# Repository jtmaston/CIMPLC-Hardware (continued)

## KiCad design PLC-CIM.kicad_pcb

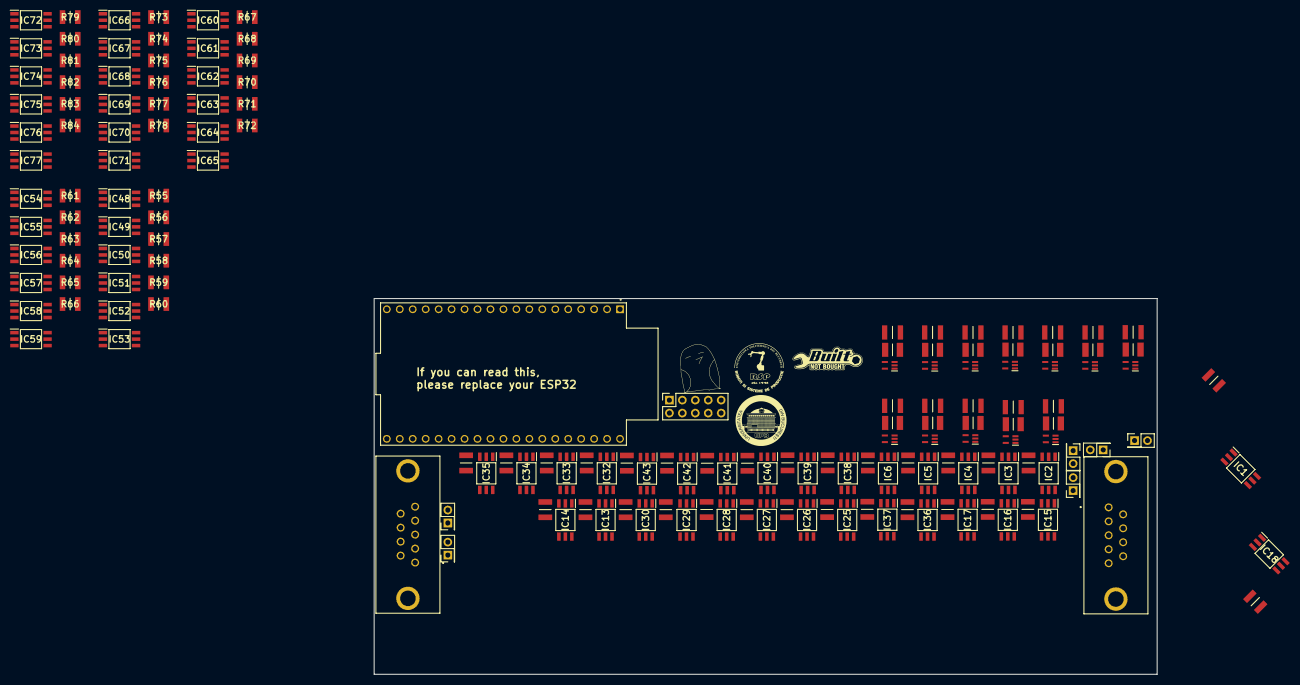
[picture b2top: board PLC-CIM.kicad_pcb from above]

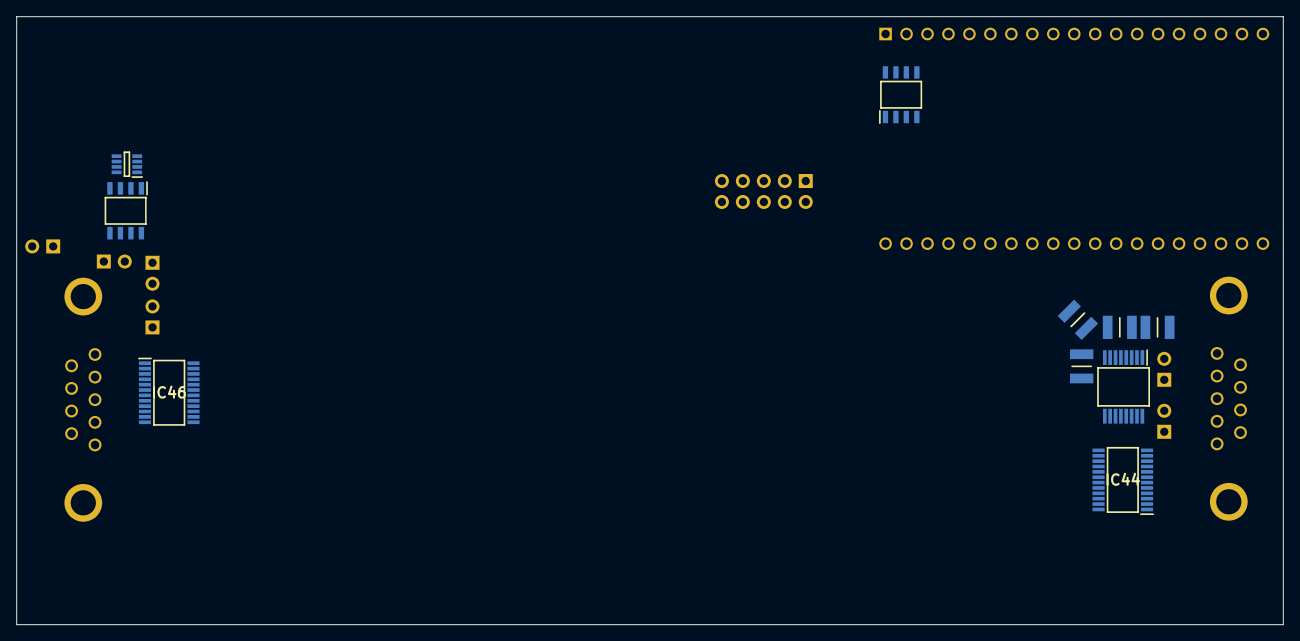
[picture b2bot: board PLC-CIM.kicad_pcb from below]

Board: 4 copper layers, 153.5 x 73.7 mm, 176 parts (10 on the bottom side), 177 nets, no tracks yet.

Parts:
C1, C2, C3, C4: 12103C104KAT2A; CAPC3325X94N
IC1, IC2, IC3, IC4, IC5, IC6, IC13, IC14, IC15, IC16, IC17, IC18, IC25, IC26, IC27, IC28, IC29, IC30, IC32, IC33, IC34, IC35, IC36, IC37, IC38, IC39, IC40, IC41, IC42, IC43, IC48, IC49, IC50, IC51, IC52, IC53, IC54, IC55, IC56, IC57, IC58, IC59, IC60, IC61, IC62, IC63, IC64, IC65, IC66, IC67, IC68, IC69, IC70, IC71, IC72, IC73, IC74, IC75, IC76, IC77: TLP172AM_TPR,E; SOIC127P700X230-6N
IC7, IC8, IC9, IC10, IC11, IC12, IC19, IC20, IC21, IC22, IC23, IC24: TLV9351IDCKR; SOT65P210X110-5N
IC31: MAX3221IDBRE4; SOP65P780X200-16N
IC44, IC46: PCA9555PW,118; SOP65P640X110-24N
IC45: TCAN337DCNR; SOT65P280X145-8N
IC47: SN65HVD75DR; SOIC127P600X175-8N
J8, J13: 750678-1; 7506781
J9, J10, J14, J15, J16, J17: Conn_02x01; PinHeader_2x01_P2.54mm_Vertical
J11: Conn_02x05_Odd_Even; PinSocket_2x05_P2.54mm_Vertical
R1, R2, R3, R4, R5, R6, R19, R20, R21, R22, R23, R24, R37, R38, R39, R40, R41, R42, R43, R44, R45, R46, R47, R48, R49, R50, R51, R52, R53, R54, R55, R56, R57, R58, R59, R60, R61, R62, R63, R64, R65, R66, R67, R68, R69, R70, R71, R72, R73, R74, R75, R76, R77, R78, R79, R80, R81, R82, R83, R84: CRCW1210267RFKEA; RESC3225X60N
R7, R8, R9, R10, R11, R12, R25, R26, R27, R28, R29, R30: RK73B2ETTD152J; RESC3226X70N
R13, R14, R15, R16, R17, R18, R31, R32, R33, R34, R35, R36: RMCF1210FT10K0; RESC3225X70N
U1: ESP32-DEVKITC; MODULE_ESP32-DEVKITC
U2: AT24CM02-SSHM-B; SOIC127P600X175-8N

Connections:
+3.3V: IC31.15 (VCC), IC44.1 (~INT), IC44.2 (A1), IC44.3 (A2), IC44.24 (VDD), IC45.3 (VCC), IC46.1 (~INT), IC46.2 (A1), IC46.3 (A2), IC46.24 (VDD), IC47.2 (~RE), IC47.8 (VCC), J11.1, U1.1 (3V3), U2.8 (VCC)
+24V: IC1.4 (DRAIN_1), IC2.4 (DRAIN_1), IC3.4 (DRAIN_1), IC4.4 (DRAIN_1), IC5.4 (DRAIN_1), IC6.4 (DRAIN_1), IC7.5 (V+), IC8.5 (V+), IC9.5 (V+), IC10.5 (V+), IC11.5 (V+), IC12.5 (V+), IC13.4 (DRAIN_1), IC14.4 (DRAIN_1), IC15.4 (DRAIN_1), IC16.4 (DRAIN_1), IC17.4 (DRAIN_1), IC18.4 (DRAIN_1), IC19.5 (V+), IC20.5 (V+), IC21.5 (V+), IC22.5 (V+), IC23.5 (V+), IC24.5 (V+), IC25.4 (DRAIN_1), IC26.4 (DRAIN_1), IC27.4 (DRAIN_1), IC28.4 (DRAIN_1), IC29.4 (DRAIN_1), IC30.4 (DRAIN_1), IC32.4 (DRAIN_1), IC33.4 (DRAIN_1), IC34.4 (DRAIN_1), IC35.4 (DRAIN_1), IC36.4 (DRAIN_1), IC37.4 (DRAIN_1), IC38.4 (DRAIN_1), IC39.4 (DRAIN_1), IC40.4 (DRAIN_1), IC41.4 (DRAIN_1), IC42.4 (DRAIN_1), IC43.4 (DRAIN_1), J17.2
/O Block 1/O_ACT_1: IC6.1 (ANODE), IC44.4 (I/O0_0), IC53.1 (ANODE)
/O Block 1/O_ACT_2: IC5.1 (ANODE), IC44.5 (I/O0_1), IC52.1 (ANODE)
/O Block 1/O_ACT_3: IC4.1 (ANODE), IC44.6 (I/O0_2), IC51.1 (ANODE)
/O Block 1/O_ACT_4: IC3.1 (ANODE), IC44.7 (I/O0_3), IC50.1 (ANODE)
/O Block 1/O_ACT_5: IC2.1 (ANODE), IC44.8 (I/O0_4), IC49.1 (ANODE)
/O Block 1/O_ACT_6: IC1.1 (ANODE), IC44.9 (I/O0_5), IC48.1 (ANODE)
/O Block 2/O_ACT_1: IC18.1 (ANODE), IC44.10 (I/O0_6), IC59.1 (ANODE)
/O Block 2/O_ACT_2: IC17.1 (ANODE), IC44.11 (I/O0_7), IC58.1 (ANODE)
/O Block 2/O_ACT_3: IC16.1 (ANODE), IC44.13 (I/O1_0), IC57.1 (ANODE)
/O Block 2/O_ACT_4: IC15.1 (ANODE), IC44.14 (I/O1_1), IC56.1 (ANODE)
/O Block 2/O_ACT_5: IC14.1 (ANODE), IC44.15 (I/O1_2), IC55.1 (ANODE)
/O Block 2/O_ACT_6: IC13.1 (ANODE), IC44.16 (I/O1_3), IC54.1 (ANODE)
/O Block 3/O_ACT_1: IC30.1 (ANODE), IC44.17 (I/O1_4), IC65.1 (ANODE)
/O Block 3/O_ACT_2: IC29.1 (ANODE), IC44.18 (I/O1_5), IC64.1 (ANODE)
/O Block 3/O_ACT_3: IC28.1 (ANODE), IC44.19 (I/O1_6), IC63.1 (ANODE)
/O Block 3/O_ACT_4: IC27.1 (ANODE), IC44.20 (I/O1_7), IC62.1 (ANODE)
/O Block 3/O_ACT_5: IC26.1 (ANODE), IC46.4 (I/O0_0), IC61.1 (ANODE)
/O Block 3/O_ACT_6: IC25.1 (ANODE), IC46.5 (I/O0_1), IC60.1 (ANODE)
/O Block 4/O_ACT_1: IC37.1 (ANODE), IC46.6 (I/O0_2), IC71.1 (ANODE)
/O Block 4/O_ACT_2: IC36.1 (ANODE), IC46.7 (I/O0_3), IC70.1 (ANODE)
/O Block 4/O_ACT_3: IC35.1 (ANODE), IC46.8 (I/O0_4), IC69.1 (ANODE)
/O Block 4/O_ACT_4: IC34.1 (ANODE), IC46.9 (I/O0_5), IC68.1 (ANODE)
/O Block 4/O_ACT_5: IC33.1 (ANODE), IC46.10 (I/O0_6), IC67.1 (ANODE)
/O Block 4/O_ACT_6: IC32.1 (ANODE), IC46.11 (I/O0_7), IC66.1 (ANODE)
/O Block 5/O_ACT_1: IC43.1 (ANODE), IC46.13 (I/O1_0), IC77.1 (ANODE)
/O Block 5/O_ACT_2: IC42.1 (ANODE), IC46.14 (I/O1_1), IC76.1 (ANODE)
/O Block 5/O_ACT_3: IC41.1 (ANODE), IC46.15 (I/O1_2), IC75.1 (ANODE)
/O Block 5/O_ACT_4: IC40.1 (ANODE), IC46.16 (I/O1_3), IC74.1 (ANODE)
/O Block 5/O_ACT_5: IC39.1 (ANODE), IC46.17 (I/O1_4), IC73.1 (ANODE)
/O Block 5/O_ACT_6: IC38.1 (ANODE), IC46.18 (I/O1_5), IC72.1 (ANODE)
ADR_1: IC44.21 (A0), U1.31 (IO19)
ADR_2: IC46.21 (A0), U1.30 (IO18)
CAN_FAULT: IC45.5 (FAULT), U1.26 (IO4)
CAN_RX: IC45.1 (TXD), U1.24 (IO2)
CAN_TX: IC45.4 (RXD), U1.25 (IO0)
FORCEOFF: IC31.12 (FORCEON), U1.29 (IO5)
FORCEON: IC31.16 (~FORCEOFF), U1.23 (IO15)
GND: C3.1, C4.2, IC7.2 (V-), IC8.2 (V-), IC9.2 (V-), IC10.2 (V-), IC11.2 (V-), IC12.2 (V-), IC19.2 (V-), IC20.2 (V-), IC21.2 (V-), IC22.2 (V-), IC23.2 (V-), IC24.2 (V-), IC31.1 (~EN), IC31.14 (GND), IC44.12 (VSS), IC45.2 (GND), IC45.8 (S), IC46.12 (VSS), IC47.3 (DE), IC47.5 (GND), IC48.4 (DRAIN_1), IC49.4 (DRAIN_1), IC50.4 (DRAIN_1), IC51.4 (DRAIN_1), IC52.4 (DRAIN_1), IC53.4 (DRAIN_1), IC54.4 (DRAIN_1), IC55.4 (DRAIN_1), IC56.4 (DRAIN_1), IC57.4 (DRAIN_1), IC58.4 (DRAIN_1), IC59.4 (DRAIN_1), IC60.4 (DRAIN_1), IC61.4 (DRAIN_1), IC62.4 (DRAIN_1), IC63.4 (DRAIN_1), IC64.4 (DRAIN_1), IC65.4 (DRAIN_1), IC66.4 (DRAIN_1), IC67.4 (DRAIN_1), IC68.4 (DRAIN_1), IC69.4 (DRAIN_1), IC70.4 (DRAIN_1), IC71.4 (DRAIN_1), IC72.4 (DRAIN_1), IC73.4 (DRAIN_1), IC74.4 (DRAIN_1), IC75.4 (DRAIN_1), IC76.4 (DRAIN_1), IC77.4 (DRAIN_1), J8.5, J8.MH1, J8.MH2, J11.2, J13.1, J13.MH1, J13.MH2, R1.2, R2.2, R3.2, R4.2, R5.2, R6.2, R7.2, R8.2, R9.2, R10.2, R11.2, R12.2, R19.2, R20.2, R21.2, R22.2, R23.2, R24.2, R25.2, R26.2, R27.2, R28.2, R29.2, R30.2, R37.2, R38.2, R39.2, R40.2, R41.2, R42.2, R43.2, R44.2, R45.2, R46.2, R47.2, R48.2, R49.2, R50.2, R51.2, R52.2, R53.2, R54.2, R55.2, R56.2, R57.2, R58.2, R59.2, R60.2, R61.2, R62.2, R63.2, R64.2, R65.2, R66.2, R67.2, R68.2, R69.2, R70.2, R71.2, R72.2, R73.2, R74.2, R75.2, R76.2, R77.2, R78.2, R79.2, R80.2, R81.2, R82.2, R83.2, R84.2, U1.14 (GND1), U1.32 (GND2), U1.38 (GND3), U2.3 (A2), U2.4 (GND), U2.7 (WP)
GPIO_1: IC6.6 (DRAIN_2), IC8.1 (IN+), IC53.6 (DRAIN_2)
GPIO_2: IC5.6 (DRAIN_2), IC7.1 (IN+), IC52.6 (DRAIN_2)
GPIO_3: IC4.6 (DRAIN_2), IC12.1 (IN+), IC51.6 (DRAIN_2)
GPIO_4: IC3.6 (DRAIN_2), IC11.1 (IN+), IC50.6 (DRAIN_2)
GPIO_5: IC2.6 (DRAIN_2), IC10.1 (IN+), IC49.6 (DRAIN_2)
GPIO_6: IC1.6 (DRAIN_2), IC9.1 (IN+), IC48.6 (DRAIN_2)
GPIO_7: IC18.6 (DRAIN_2), IC20.1 (IN+), IC59.6 (DRAIN_2)
GPIO_8: IC17.6 (DRAIN_2), IC19.1 (IN+), IC58.6 (DRAIN_2)
GPIO_9: IC16.6 (DRAIN_2), IC24.1 (IN+), IC57.6 (DRAIN_2)
GPIO_10: IC15.6 (DRAIN_2), IC23.1 (IN+), IC56.6 (DRAIN_2)
GPIO_11: IC14.6 (DRAIN_2), IC22.1 (IN+), IC55.6 (DRAIN_2)
GPIO_12: IC13.6 (DRAIN_2), IC21.1 (IN+), IC54.6 (DRAIN_2)
MCU_IN_1: R27.1, R33.2, U1.4 (SENSOR_VN)
MCU_IN_2: R28.1, R34.2, U1.3 (SENSOR_VP)
MCU_IN_3: R29.1, R35.2, U1.9 (IO25)
MCU_IN_4: R30.1, R36.2, U1.8 (IO33)
MCU_IN_5: R25.1, R31.2, U1.7 (IO32)
MCU_IN_6: R26.1, R32.2, U1.6 (IO35)
MCU_IN_7: R9.1, R15.2, U1.5 (IO34)
MCU_IN_8: R10.1, R16.2, U1.10 (IO26)
MCU_IN_9: R11.1, R17.2, U1.11 (IO27)
MCU_IN_10: R12.1, R18.2, U1.12 (IO14)
MCU_IN_11: R7.1, R13.2, U1.13 (IO12)
MCU_IN_12: R8.1, R14.2, U1.15 (IO13)
unnamed: IC1.3 (CATHODE), R1.1
unnamed: IC2.3 (CATHODE), R2.1
unnamed: IC3.3 (CATHODE), R3.1
unnamed: IC4.3 (CATHODE), R4.1
unnamed: IC5.3 (CATHODE), R5.1
unnamed: IC6.3 (CATHODE), R6.1
unnamed: IC7.3 (IN-), IC7.4 (OUT), R13.1
unnamed: IC8.3 (IN-), IC8.4 (OUT), R14.1
unnamed: IC9.3 (IN-), IC9.4 (OUT), R15.1
unnamed: IC10.3 (IN-), IC10.4 (OUT), R16.1
unnamed: IC11.3 (IN-), IC11.4 (OUT), R17.1
unnamed: IC12.3 (IN-), IC12.4 (OUT), R18.1
unnamed: IC13.3 (CATHODE), R19.1
unnamed: IC14.3 (CATHODE), R20.1
unnamed: IC15.3 (CATHODE), R21.1
unnamed: IC16.3 (CATHODE), R22.1
unnamed: IC17.3 (CATHODE), R23.1
unnamed: IC18.3 (CATHODE), R24.1
unnamed: IC19.3 (IN-), IC19.4 (OUT), R31.1
unnamed: IC20.3 (IN-), IC20.4 (OUT), R32.1
unnamed: IC21.3 (IN-), IC21.4 (OUT), R33.1
unnamed: IC22.3 (IN-), IC22.4 (OUT), R34.1
unnamed: IC23.3 (IN-), IC23.4 (OUT), R35.1
unnamed: IC24.3 (IN-), IC24.4 (OUT), R36.1
unnamed: IC25.3 (CATHODE), R37.1
unnamed: IC26.3 (CATHODE), R38.1
unnamed: IC27.3 (CATHODE), R39.1
unnamed: IC28.3 (CATHODE), R40.1
unnamed: IC29.3 (CATHODE), R41.1
unnamed: IC30.3 (CATHODE), R42.1
unnamed: C1.2, IC31.2 (C1+)
unnamed: C1.1, IC31.4 (C1-)
unnamed: C2.2, IC31.5 (C2+)
unnamed: C2.1, IC31.6 (C2-)
unnamed: IC31.13 (DOUT), J9.1
unnamed: IC31.8 (RIN), J10.1
unnamed: C3.2, IC31.3 (V+)
unnamed: C4.1, IC31.7 (V-)
unnamed: IC32.3 (CATHODE), R43.1
unnamed: IC33.3 (CATHODE), R44.1
unnamed: IC34.3 (CATHODE), R45.1
unnamed: IC35.3 (CATHODE), R46.1
unnamed: IC36.3 (CATHODE), R47.1
unnamed: IC37.3 (CATHODE), R48.1
unnamed: IC38.3 (CATHODE), R49.1
unnamed: IC39.3 (CATHODE), R50.1
unnamed: IC40.3 (CATHODE), R51.1
unnamed: IC41.3 (CATHODE), R52.1
unnamed: IC42.3 (CATHODE), R53.1
unnamed: IC43.3 (CATHODE), R54.1
unnamed: IC47.6 (A), J15.1
unnamed: IC47.7 (B), J14.1
unnamed: IC48.3 (CATHODE), R55.1
unnamed: IC49.3 (CATHODE), R56.1
unnamed: IC50.3 (CATHODE), R57.1
unnamed: IC51.3 (CATHODE), R58.1
unnamed: IC52.3 (CATHODE), R59.1
unnamed: IC53.3 (CATHODE), R60.1
unnamed: IC54.3 (CATHODE), R61.1
unnamed: IC55.3 (CATHODE), R62.1
unnamed: IC56.3 (CATHODE), R63.1
unnamed: IC57.3 (CATHODE), R64.1
unnamed: IC58.3 (CATHODE), R65.1
unnamed: IC59.3 (CATHODE), R66.1
unnamed: IC60.3 (CATHODE), R67.1
unnamed: IC61.3 (CATHODE), R68.1
unnamed: IC62.3 (CATHODE), R69.1
unnamed: IC63.3 (CATHODE), R70.1
unnamed: IC64.3 (CATHODE), R71.1
unnamed: IC65.3 (CATHODE), R72.1
unnamed: IC66.3 (CATHODE), R73.1
unnamed: IC67.3 (CATHODE), R74.1
unnamed: IC68.3 (CATHODE), R75.1
unnamed: IC69.3 (CATHODE), R76.1
unnamed: IC70.3 (CATHODE), R77.1
unnamed: IC71.3 (CATHODE), R78.1
unnamed: IC72.3 (CATHODE), R79.1
unnamed: IC73.3 (CATHODE), R80.1
unnamed: IC74.3 (CATHODE), R81.1
unnamed: IC75.3 (CATHODE), R82.1
unnamed: IC76.3 (CATHODE), R83.1
unnamed: IC77.3 (CATHODE), R84.1
unnamed: J8.2, J9.2
unnamed: J8.3, J10.2
unnamed: J13.3, J14.2
unnamed: J13.8, J15.2
unnamed: J13.6, J16.1
unnamed: J13.7, J17.1
OUT_13: IC30.6 (DRAIN_2), IC65.6 (DRAIN_2)
OUT_14: IC29.6 (DRAIN_2), IC64.6 (DRAIN_2)
OUT_15: IC28.6 (DRAIN_2), IC63.6 (DRAIN_2)
OUT_16: IC27.6 (DRAIN_2), IC62.6 (DRAIN_2)
OUT_17: IC26.6 (DRAIN_2), IC61.6 (DRAIN_2)
OUT_18: IC25.6 (DRAIN_2), IC60.6 (DRAIN_2)
OUT_19: IC37.6 (DRAIN_2), IC71.6 (DRAIN_2)
OUT_20: IC36.6 (DRAIN_2), IC70.6 (DRAIN_2)
OUT_21: IC35.6 (DRAIN_2), IC69.6 (DRAIN_2)
OUT_22: IC34.6 (DRAIN_2), IC68.6 (DRAIN_2)
OUT_23: IC33.6 (DRAIN_2), IC67.6 (DRAIN_2)
OUT_24: IC32.6 (DRAIN_2), IC66.6 (DRAIN_2)
OUT_25: IC43.6 (DRAIN_2), IC77.6 (DRAIN_2)
OUT_26: IC42.6 (DRAIN_2), IC76.6 (DRAIN_2)
OUT_27: IC41.6 (DRAIN_2), IC75.6 (DRAIN_2)
OUT_28: IC40.6 (DRAIN_2), IC74.6 (DRAIN_2)
OUT_29: IC39.6 (DRAIN_2), IC73.6 (DRAIN_2)
OUT_30: IC38.6 (DRAIN_2), IC72.6 (DRAIN_2)
RS232_STATUS: IC31.10 (~INVALID), U1.37 (IO23)
RX0: IC31.9 (ROUT), U1.34 (RXD0)
RX1: IC47.1 (R), U1.27 (IO16)
SCL: IC44.22 (SCL), IC46.22 (SCL), J11.5, U1.36 (IO22), U2.6 (SCL)
SDA: IC44.23 (SDA), IC46.23 (SDA), J11.6, U1.33 (IO21), U2.5 (SDA)
TX0: IC31.11 (DIN), U1.35 (TXD0)
TX1: IC47.4 (D), U1.28 (IO17)

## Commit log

2023-06-10 Removed firmware files
2023-06-11 Cleaned up the repository
2023-06-11 Update LICENSE
2023-06-25 Automate library addition * Added script to automagically extract samacsys libraries and put them in corresponding folders. * Note: Requires zsh
2023-11-12 something
2023-12-05 Testing documentation
2023-12-05 Prepare documentation for writerside
2023-12-05 Testing writerside documentation
2023-12-05 add action
2023-12-05 Moved dirs around
2023-12-05 Re-add docfiles
2023-12-05 Build documentation
2023-12-05 Deprecate github
2023-12-05 Separate v1 and v2 development
2023-12-05 cleanup
2023-12-05 Remove github action
2023-12-05 Update docs
2023-12-08 Update views, to make drawing sheets smaller where necessary
2024-04-08 Start proper work on V2.1
    - Replaced all blocks
    - Added input blocks
    - Added output blocks
    - Added initial CAD placement
    - Added initial routing
    - General system stability improvements to enhance the user's experience
